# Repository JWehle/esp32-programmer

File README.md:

# esp32-programmer
USB based ESP32 microcontroller programming board with boot pins.

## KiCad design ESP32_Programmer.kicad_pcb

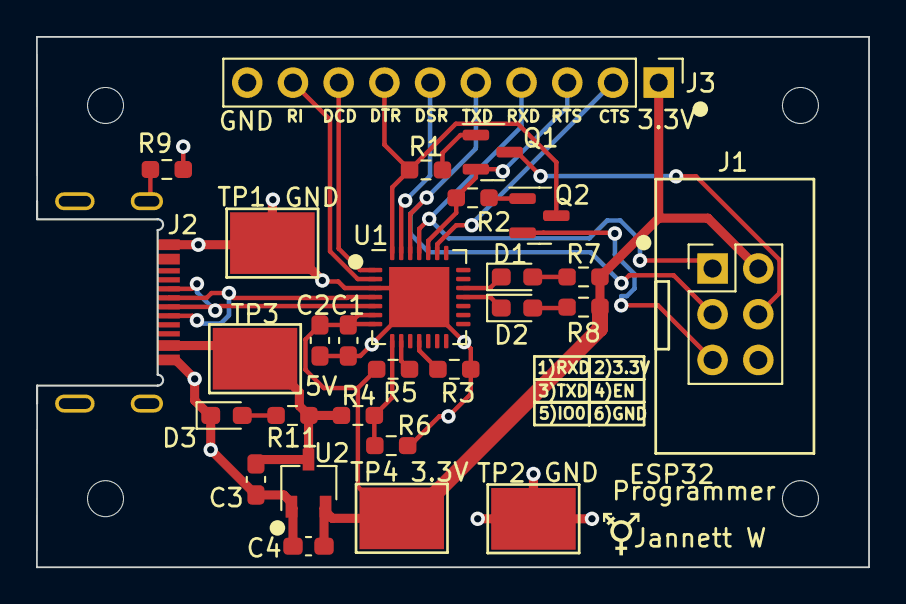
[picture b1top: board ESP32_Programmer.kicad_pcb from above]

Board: 2 copper layers, 46.2 x 29.4 mm, 33 parts (0 on the bottom side), 26 nets.

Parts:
C1: 0.1uF; C_0603_1608Metric_Pad1.08x0.95mm_HandSolder
C2, C3, C4: 10uF; C_0603_1608Metric_Pad1.08x0.95mm_HandSolder
D1, D2, D3: GREEN LED; LED_0603_1608Metric_Pad1.05x0.95mm_HandSolder
H1, H2, H3, H4: M2; MountingHole_2.0mm
J1: BHR-06-VUA; PinHeader_2x03_P2.54mm_Vertical
J2: GSB1C4621DS2HR; USB_C_Receptacle_GSB1C4621DS2HR
J3: Conn_01x10; PinHeader_1x10_P2.54mm_Vertical
Q1, Q2: MMBT3904; SOT-23
R1, R2, R3: 10K; R_0603_1608Metric_Pad0.98x0.95mm_HandSolder
R4: 22.1K; R_0603_1608Metric_Pad0.98x0.95mm_HandSolder
R5, R7, R8, R11: 2K; R_0603_1608Metric_Pad0.98x0.95mm_HandSolder
R6: 47.5K; R_0603_1608Metric_Pad0.98x0.95mm_HandSolder
R9: 1Meg; R_0603_1608Metric_Pad0.98x0.95mm_HandSolder
SYMBOL1: Trans_Symbol
TP1, TP2, TP3, TP4: 5016; TestPoint_Keystone_5016_Compact
U1: CP2102N-Axx-xQFN28; QFN-28-1EP_5x5mm_P0.5mm_EP3.35x3.35mm
U2: AP2138N-3.3TRG1; TSOT-23

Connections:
+3.3V: C1.1, C2.1, C4.1, J1.2, J3.1, R5.1, R7.1, R8.1, TP4.1, U1.6 (VDD), U1.7 (VREGIN), U2.2 (VO)
+5V: C3.1, J2.A4 (VBUS), J2.A9 (VBUS), J2.B4 (VBUS), J2.B9 (VBUS), R4.1, R11.1, TP3.1, U2.3 (VI)
CTS: J3.2, U1.23 (~CTS)
DCD: J3.8, U1.1 (~DCD)
DSR: J3.6, U1.27 (~DSR)
DTR: J3.7, Q2.3 (C), R1.2, U1.28 (~DTR)
ESP32_BOOT0: J1.5, Q2.2 (E)
ESP32_EN: J1.4, Q1.3 (C)
GND: C1.2, C2.2, C3.2, C4.2, D3.1 (K), J1.6, J2.A1 (GND), J2.A12 (GND), J2.B1 (GND), J2.B12 (GND), J3.10, R3.1, R6.2, R9.2, TP1.1, TP2.1, U1.3 (GND), U1.29 (GND), U2.1 (GND)
unnamed: D1.2 (A), R7.2
unnamed: D1.1 (K), U1.19 (~TXT/GPIO.0)
unnamed: D2.2 (A), R8.2
unnamed: D2.1 (K), U1.18 (~RXT/GPIO.1)
unnamed: D3.2 (A), R11.2
unnamed: J2.S1 (SHIELD), R9.1
unnamed: Q1.1 (B), R1.1
unnamed: Q2.1 (B), R2.1
unnamed: J2.A6 (D+), J2.B6 (D+), U1.4 (D+)
unnamed: J2.A7 (D-), J2.B7 (D-), U1.5 (D-)
unnamed: R4.2, R6.1, U1.8 (VBUS)
unnamed: R5.2, U1.9 (~RST)
unnamed: R3.2, U1.11 (~SUSPEND)
RI: J3.9, U1.2 (~RI/CLK)
RTS: J3.3, Q1.2 (E), R2.2, U1.24 (~RTS)
RXD: J1.1, J3.4, U1.25 (RXD)
TXD: J1.3, J3.5, U1.26 (TXD)

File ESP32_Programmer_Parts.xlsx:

Reference | Value | Package | Part Number | Voltage | Qty
C1 | 0.1uF | 603 |  | 10V | 1
C2-C4 | 10uF | 603 |  | 10V | 3
D1-D3 | GREEN LED | 603 |  |  | 3
H1-H4 | M2 |  |  |  | 4
J1 | BHR-06-VUA |  |  |  | 1
J2 | GSB1C4621DS2HR |  |  |  | 1
J3 | Conn_01x10 |  |  |  | 1
Q1, Q2 | MMBT3904 |  |  |  | 2
R1-R3 | 10K | 603 |  |  | 3
R4 | 22.1K | 603 |  |  | 1
R5, R7, R8, R11 | 2K | 603 |  |  | 4
R6 | 47.5K | 603 |  |  | 1
R9 | 1Meg | 603 |  |  | 1
TP1-TP4 | 5016 | 5016 | 5016 |  | 4
U1 | CP2102N-Axx-xQFN28 |  |  |  | 1
U2 | AP2138N-3.3TRG1 | SOT-23-3 | AP2138N-3.3TRG1 |  | 1
